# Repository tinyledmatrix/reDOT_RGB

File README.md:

# reDOT_RGB
Files for reDOT_RGB SAO PCB. 

Some blinking little PCB. It is a 5x7 RGB LED Matrix wit a size of 8x11mm.
See full Documentation here: 
https://hackaday.io/project/197898

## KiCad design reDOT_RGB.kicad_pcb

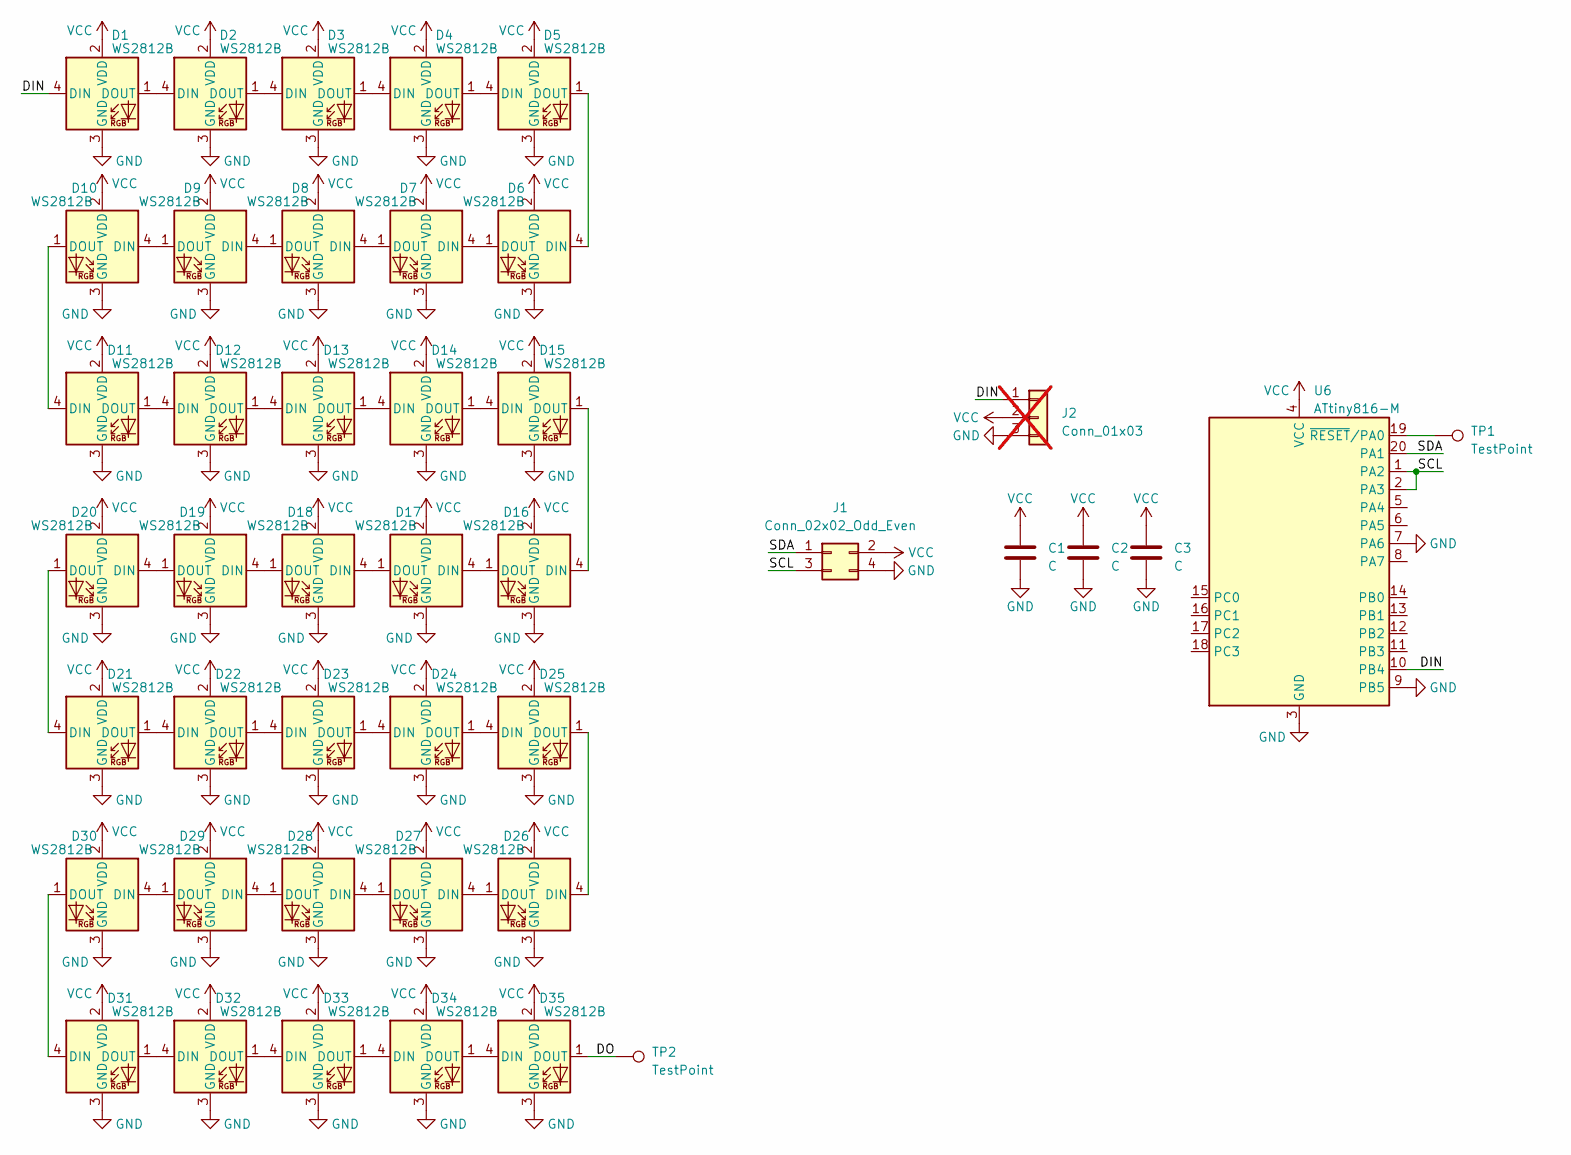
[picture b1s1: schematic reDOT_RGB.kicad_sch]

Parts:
C1, C2, C3: C; C_0402_min
D1, D2, D3, D4, D5, D6, D7, D8, D9, D10, D11, D12, D13, D14, D15, D16, D17, D18, D19, D20, D21, D22, D23, D24, D25, D26, D27, D28, D29, D30, D31, D32, D33, D34, D35: WS2812B; LED_XL-1010RGBC-WS2812B
J1: Conn_02x02_Odd_Even; PinHeader_2x02_P2.54mm_Vertical_SMD
J2: Conn_01x03; PinHeader_1x03_P2.54mm_Vertical; not fitted
TP1: TestPoint; TestPoint_Pad_D1.0mm
TP2: TestPoint; TestPoint_Pad_1.0x1.0mm
U6: ATtiny816-M; VQFN-20-1EP_3x3mm_P0.4mm_EP1.7x1.7mm

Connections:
/DIN: D1.4 (DIN), J2.1, U6.10 (PB4)
/DO: D35.1 (DOUT), TP2.1
/SCL: J1.3, U6.1 (PA2), U6.2 (PA3)
/SDA: J1.1, U6.20 (PA1)
GND: C1.2, C2.2, C3.2, D1.3 (GND), D2.3 (GND), D3.3 (GND), D4.3 (GND), D5.3 (GND), D6.3 (GND), D7.3 (GND), D8.3 (GND), D9.3 (GND), D10.3 (GND), D11.3 (GND), D12.3 (GND), D13.3 (GND), D14.3 (GND), D15.3 (GND), D16.3 (GND), D17.3 (GND), D18.3 (GND), D19.3 (GND), D20.3 (GND), D21.3 (GND), D22.3 (GND), D23.3 (GND), D24.3 (GND), D25.3 (GND), D26.3 (GND), D27.3 (GND), D28.3 (GND), D29.3 (GND), D30.3 (GND), D31.3 (GND), D32.3 (GND), D33.3 (GND), D34.3 (GND), D35.3 (GND), J1.4, J2.3, U6.3 (GND), U6.7 (PA6), U6.9 (PB5), U6.21 (GND)
unnamed: D1.1 (DOUT), D2.4 (DIN)
unnamed: D2.1 (DOUT), D3.4 (DIN)
unnamed: D3.1 (DOUT), D4.4 (DIN)
unnamed: D4.1 (DOUT), D5.4 (DIN)
unnamed: D5.1 (DOUT), D6.4 (DIN)
unnamed: D6.1 (DOUT), D7.4 (DIN)
unnamed: D7.1 (DOUT), D8.4 (DIN)
unnamed: D8.1 (DOUT), D9.4 (DIN)
unnamed: D9.1 (DOUT), D10.4 (DIN)
unnamed: D10.1 (DOUT), D11.4 (DIN)
unnamed: D11.1 (DOUT), D12.4 (DIN)
unnamed: D12.1 (DOUT), D13.4 (DIN)
unnamed: D13.1 (DOUT), D14.4 (DIN)
unnamed: D14.1 (DOUT), D15.4 (DIN)
unnamed: D15.1 (DOUT), D16.4 (DIN)
unnamed: D16.1 (DOUT), D17.4 (DIN)
unnamed: D17.1 (DOUT), D18.4 (DIN)
unnamed: D18.1 (DOUT), D19.4 (DIN)
unnamed: D19.1 (DOUT), D20.4 (DIN)
unnamed: D20.1 (DOUT), D21.4 (DIN)
unnamed: D21.1 (DOUT), D22.4 (DIN)
unnamed: D22.1 (DOUT), D23.4 (DIN)
unnamed: D23.1 (DOUT), D24.4 (DIN)
unnamed: D24.1 (DOUT), D25.4 (DIN)
unnamed: D25.1 (DOUT), D26.4 (DIN)
unnamed: D26.1 (DOUT), D27.4 (DIN)
unnamed: D27.1 (DOUT), D28.4 (DIN)
unnamed: D28.1 (DOUT), D29.4 (DIN)
unnamed: D29.1 (DOUT), D30.4 (DIN)
unnamed: D30.1 (DOUT), D31.4 (DIN)
unnamed: D31.1 (DOUT), D32.4 (DIN)
unnamed: D32.1 (DOUT), D33.4 (DIN)
unnamed: D33.1 (DOUT), D34.4 (DIN)
unnamed: D34.1 (DOUT), D35.4 (DIN)
unnamed: TP1.1, U6.19 (~RESET/PA0)
VCC: C1.1, C2.1, C3.1, D1.2 (VDD), D2.2 (VDD), D3.2 (VDD), D4.2 (VDD), D5.2 (VDD), D6.2 (VDD), D7.2 (VDD), D8.2 (VDD), D9.2 (VDD), D10.2 (VDD), D11.2 (VDD), D12.2 (VDD), D13.2 (VDD), D14.2 (VDD), D15.2 (VDD), D16.2 (VDD), D17.2 (VDD), D18.2 (VDD), D19.2 (VDD), D20.2 (VDD), D21.2 (VDD), D22.2 (VDD), D23.2 (VDD), D24.2 (VDD), D25.2 (VDD), D26.2 (VDD), D27.2 (VDD), D28.2 (VDD), D29.2 (VDD), D30.2 (VDD), D31.2 (VDD), D32.2 (VDD), D33.2 (VDD), D34.2 (VDD), D35.2 (VDD), J1.2, J2.2, U6.4 (VCC)

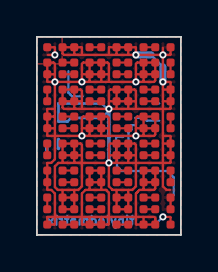
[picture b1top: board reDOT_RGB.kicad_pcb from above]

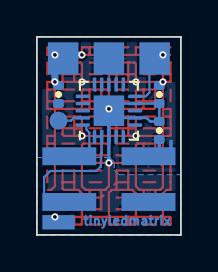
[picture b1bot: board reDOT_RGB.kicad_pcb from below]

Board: 2 copper layers, 8.0 x 11.0 mm, 43 parts (8 on the bottom side), 41 nets.

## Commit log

2024-10-14 Added images of PCB
2024-10-14 Added PCB files
2024-10-14 Some Firmwre for Testing
    Does include platformIO Project
2024-11-01 Test-Firmware
2024-11-12 minor chnage
